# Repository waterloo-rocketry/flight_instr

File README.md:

# flight_instr
This is the flight/engine instrumentation system used in Waterloo Rocketry's 2018 rocket, _Unexploded Ordnance (UXO)_. This repository tracks the hardware and software used in this system. The flight instrumentation PCB is a monolithic board containing an Arduino Nano, an SD card, a digital sensor suite, an analog sensor suite, a radio transceiver, and an H-bridge valve driver. Two copies of this board were used in UXO to successfully launch the rocket to 13000 ft.

This system is no longer in use. It has been replaced by RocketCAN, a collection of boards that implement the functionality of flight instrumentation in a modular manner. The new system is tracked in the `canhw`, `canlib`, and `cansw_*` repositories.

## Injector board assembly

## Vent board assembly

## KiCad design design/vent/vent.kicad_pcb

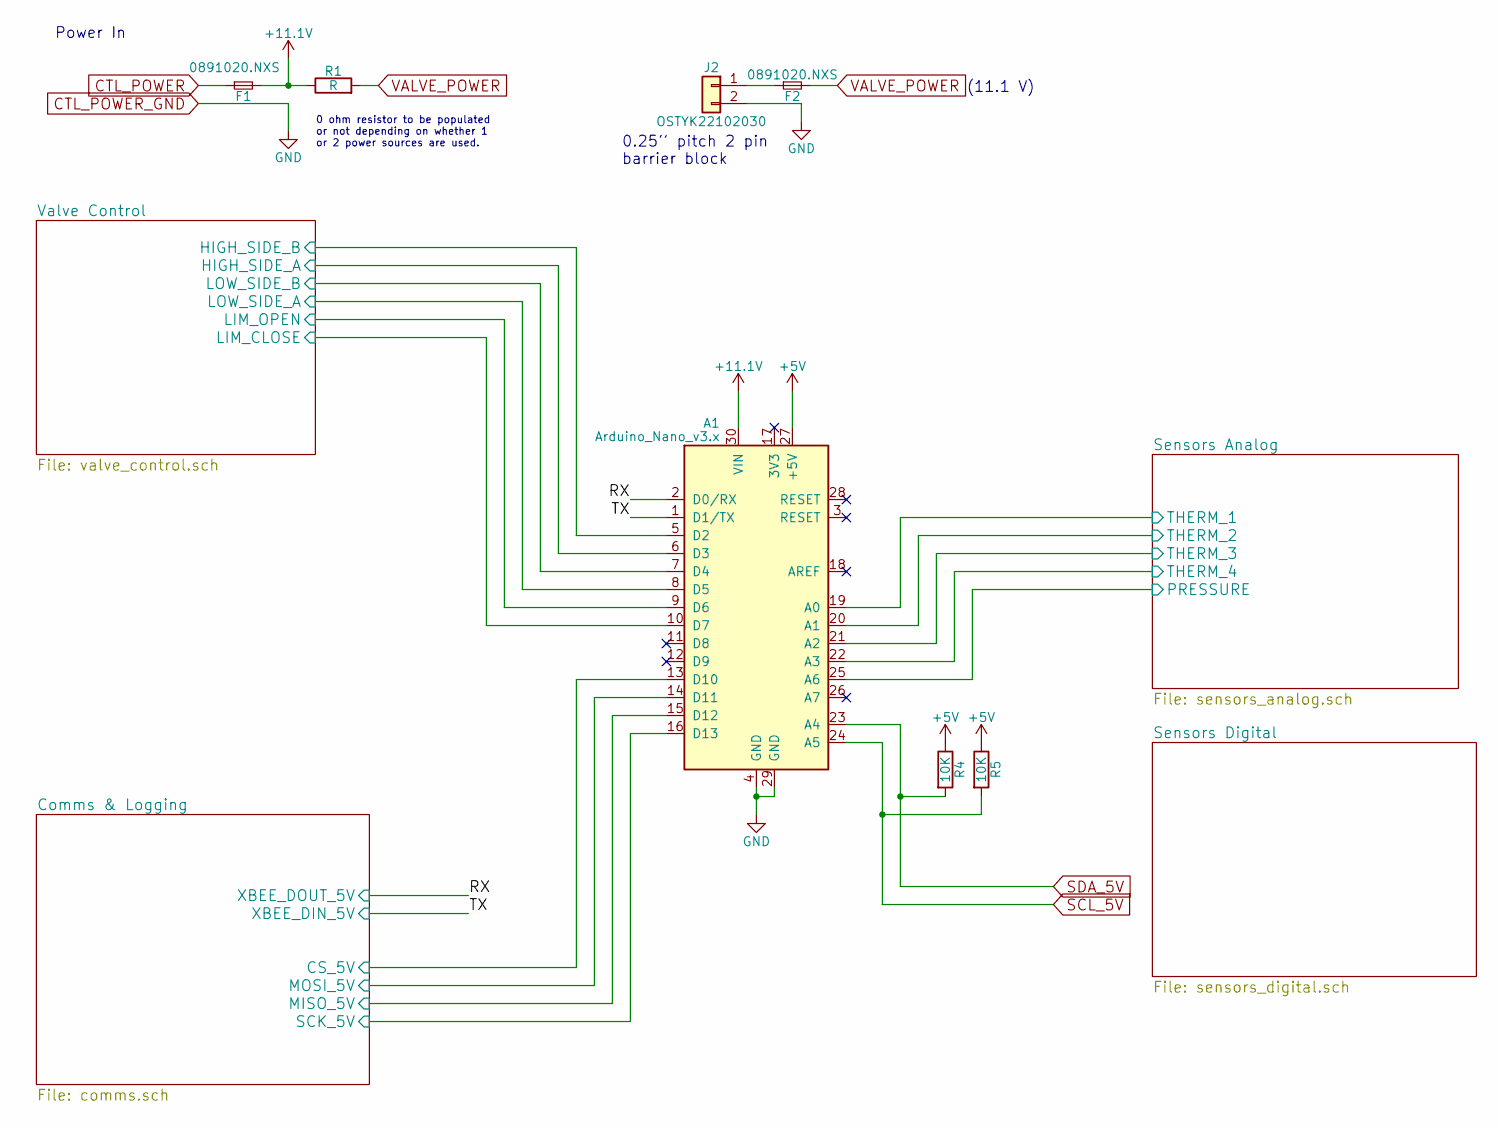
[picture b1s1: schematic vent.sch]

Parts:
A1: Arduino_Nano_v3.x; Arduino_Nano
F1, F2: 0891020.NXS; PC_AutoFuse_Holder
J2: OSTYK22102030; Barrier_Strip_2Circuit
R1: R; R_0805_HandSoldering
R4, R5: 10K; R_0805_HandSoldering

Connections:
+5V: A1.27 (+5V), R4.1, R5.1; also elsewhere on the board
+11.1V: A1.30 (VIN), F1.2, R1.1; also elsewhere on the board
/Comms & Logging/CS_5V: A1.13 (D10); also elsewhere on the board
/Comms & Logging/MISO_5V: A1.15 (D12); also elsewhere on the board
/Comms & Logging/MOSI_5V: A1.14 (D11); also elsewhere on the board
/Comms & Logging/SCK_5V: A1.16 (D13); also elsewhere on the board
/RX: A1.2 (D0/RX); also elsewhere on the board
/Sensors Analog/PRESSURE: A1.25 (A6); also elsewhere on the board
/Sensors Analog/THERM_1: A1.19 (A0); also elsewhere on the board
/Sensors Analog/THERM_2: A1.20 (A1); also elsewhere on the board
/Sensors Analog/THERM_3: A1.21 (A2); also elsewhere on the board
/Sensors Analog/THERM_4: A1.22 (A3); also elsewhere on the board
/TX: A1.1 (D1/TX); also elsewhere on the board
/Valve Control/HIGH_SIDE_A: A1.6 (D3); also elsewhere on the board
/Valve Control/HIGH_SIDE_B: A1.5 (D2); also elsewhere on the board
/Valve Control/LIM_CLOSE: A1.10 (D7); also elsewhere on the board
/Valve Control/LIM_OPEN: A1.9 (D6); also elsewhere on the board
/Valve Control/LOW_SIDE_A: A1.8 (D5); also elsewhere on the board
/Valve Control/LOW_SIDE_B: A1.7 (D4); also elsewhere on the board
CTL_POWER: F1.1; also elsewhere on the board
CTL_POWER_GND: A1.4 (GND), A1.29 (GND), J2.2; also elsewhere on the board
unnamed: F2.1, J2.1
SCL_5V: A1.24 (A5), R5.2; also elsewhere on the board
SDA_5V: A1.23 (A4), R4.2; also elsewhere on the board
VALVE_POWER: F2.2, R1.2; also elsewhere on the board

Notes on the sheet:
Power In
(11.1 V)
0 ohm resistor to be populated or not depending on whether 1 or 2 power sources are used.
0.25'' pitch 2 pin barrier block

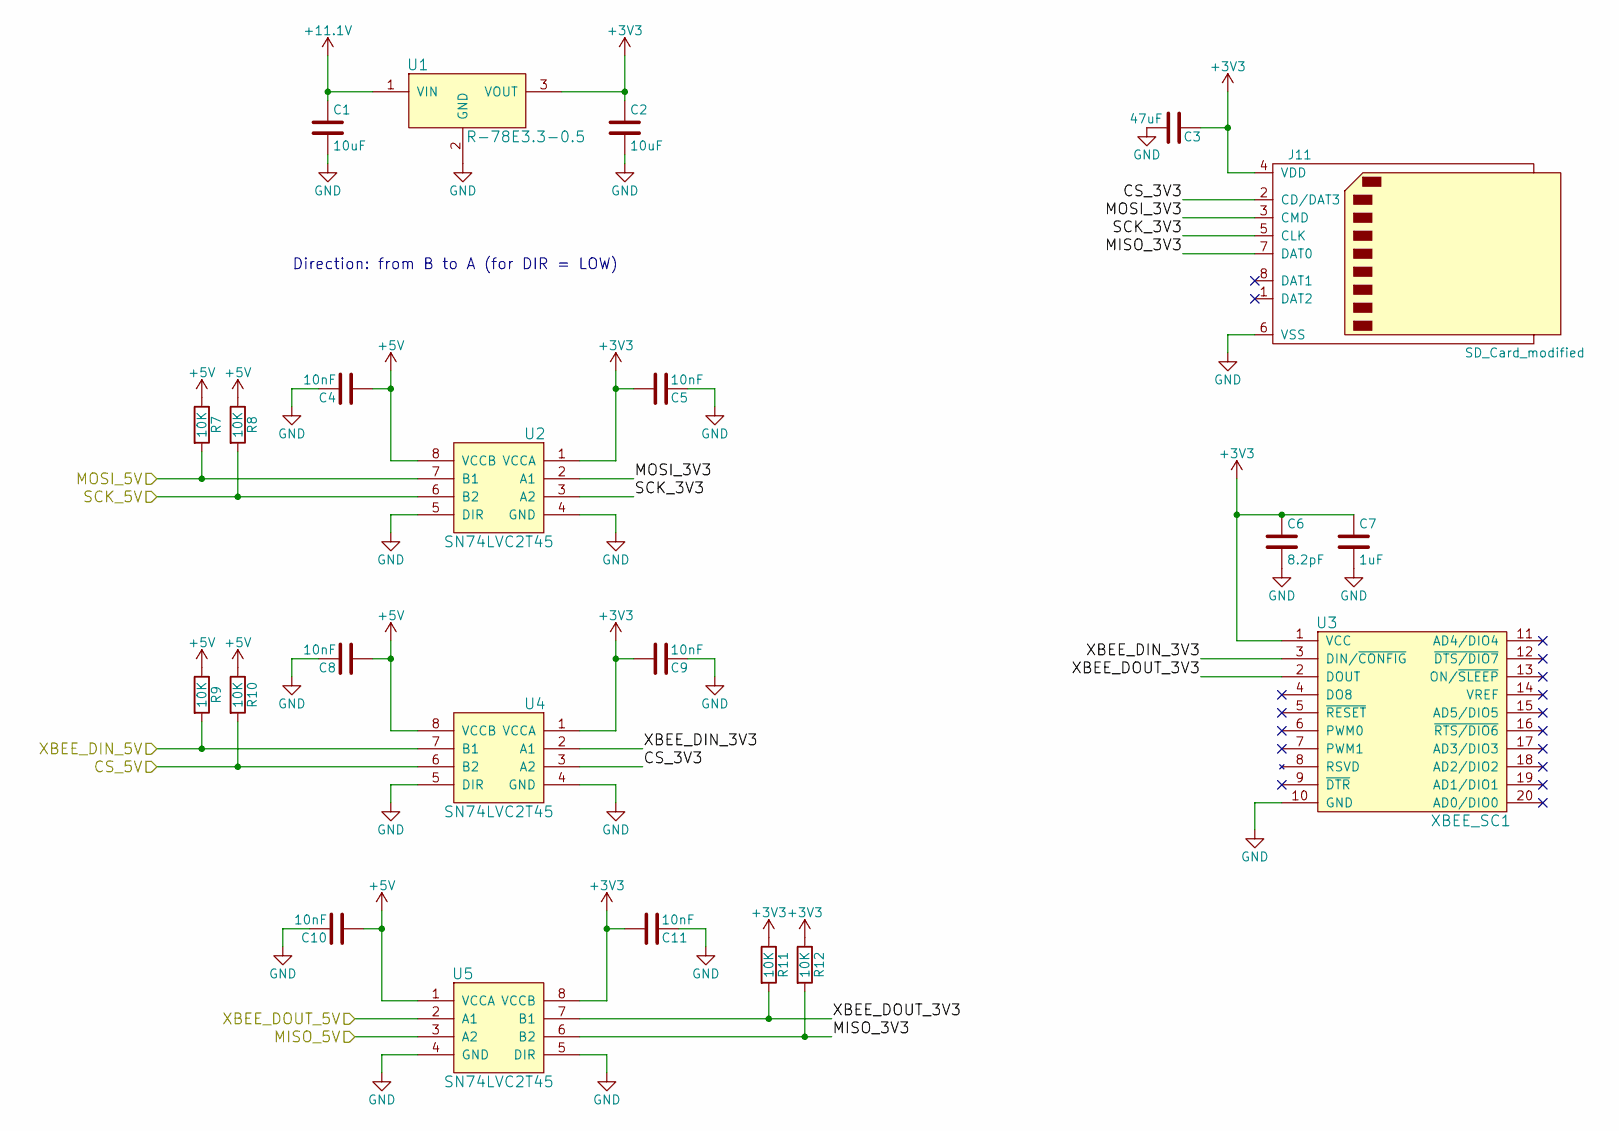
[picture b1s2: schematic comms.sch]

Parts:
C1, C2: 10uF; C_0805_HandSoldering
C3: 47uF; CP_Radial_Tantal_D5.0mm_P2.50mm
C4, C5, C8, C9, C10, C11: 10nF; C_0805_HandSoldering
C6: 8.2pF; C_0805_HandSoldering
C7: 1uF; C_0805_HandSoldering
J11: SD_Card_modified; WM6698CT-ND
R7, R8, R9, R10, R11, R12: 10K; R_0805_HandSoldering
U1: R-78E3.3-0.5; SIP3_11.6x8.5mm
U2, U4, U5: SN74LVC2T45; TSSOP-8_3x3mm_Pitch0.65mm
U3: XBEE_SC1; Xbee_SC1

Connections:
+3V3: C2.1, C3.1, C5.2, C6.1, C7.1, C9.2, C11.2, J11.4 (VDD), R11.1, R12.1, U1.3 (VOUT), U2.1 (VCCA), U3.1 (VCC), U4.1 (VCCA), U5.8 (VCCB)
+5V: C4.2, C8.2, C10.2, R7.1, R8.1, R9.1, R10.1, U2.8 (VCCB), U4.8 (VCCB), U5.1 (VCCA); also elsewhere on the board
+11.1V: C1.1, U1.1 (VIN); also elsewhere on the board
/Comms & Logging/CS_3V3: J11.2 (CD/DAT3), U4.3 (A2)
/Comms & Logging/CS_5V: R10.2, U4.6 (B2); also elsewhere on the board
/Comms & Logging/MISO_3V3: J11.7 (DAT0), R12.2, U5.6 (B2)
/Comms & Logging/MISO_5V: U5.3 (A2); also elsewhere on the board
/Comms & Logging/MOSI_3V3: J11.3 (CMD), U2.2 (A1)
/Comms & Logging/MOSI_5V: R7.2, U2.7 (B1); also elsewhere on the board
/Comms & Logging/SCK_3V3: J11.5 (CLK), U2.3 (A2)
/Comms & Logging/SCK_5V: R8.2, U2.6 (B2); also elsewhere on the board
/Comms & Logging/XBEE_DIN_3V3: U3.3 (DIN/~CONFIG), U4.2 (A1)
/Comms & Logging/XBEE_DOUT_3V3: R11.2, U3.2 (DOUT), U5.7 (B1)
/RX: U5.2 (A1); also elsewhere on the board
/TX: R9.2, U4.7 (B1); also elsewhere on the board
CTL_POWER_GND: C1.2, C2.2, C3.2, C4.1, C5.1, C6.2, C7.2, C8.1, C9.1, C10.1, C11.1, J11.6 (VSS), U1.2 (GND), U2.4 (GND), U2.5 (DIR), U3.10 (GND), U4.4 (GND), U4.5 (DIR), U5.4 (GND), U5.5 (DIR); also elsewhere on the board

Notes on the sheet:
Direction: from B to A (for DIR = LOW)

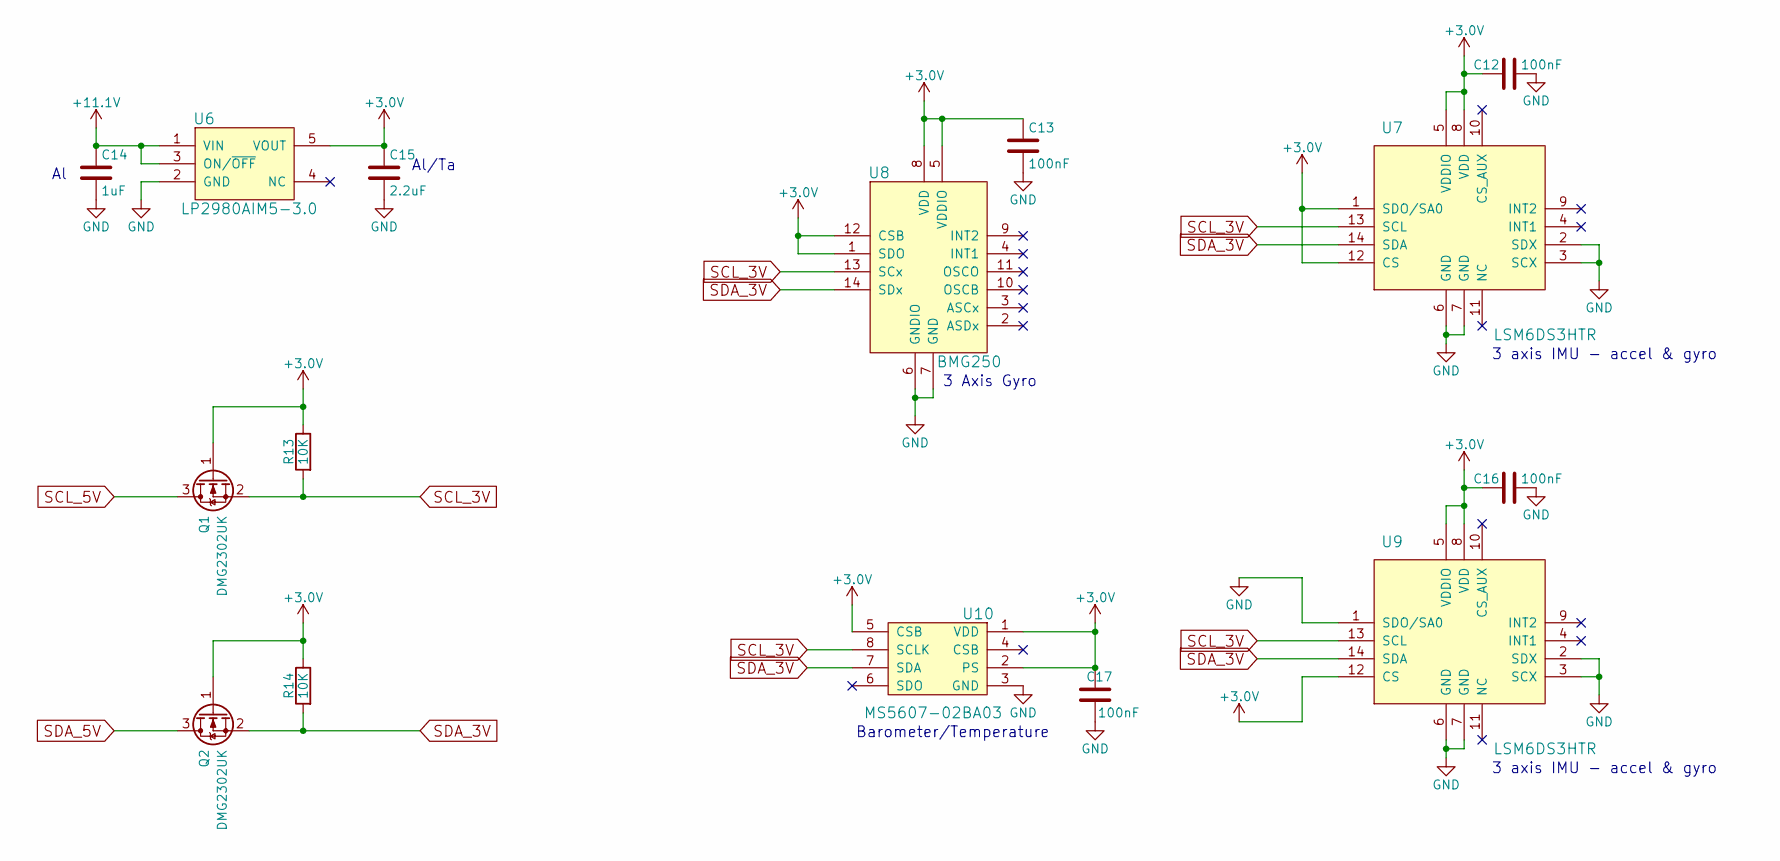
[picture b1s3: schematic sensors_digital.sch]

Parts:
C12, C13, C16, C17: 100nF; C_0805_HandSoldering
C14: 1uF; CP_Radial_Tantal_D5.0mm_P2.50mm
C15: 2.2uF; CP_Radial_Tantal_D5.0mm_P2.50mm
Q1, Q2: DMG2302UK; SOT-23_Handsoldering
R13, R14: 10K; R_0805_HandSoldering
U6: LP2980AIM5-3.0; SOT-23-5_HandSoldering
U7, U9: LSM6DS3HTR
U8: BMG250; Bosch_LGA-14
U10: MS5607-02BA03; MS560702BA03

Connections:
+3.0V: C12.1, C13.1, C15.1, C16.1, C17.1, Q1.1 (G), Q2.1 (G), R13.1, R14.1, U6.5 (VOUT), U7.1 (SDO/SA0), U7.5 (VDDIO), U7.8 (VDD), U7.12 (CS), U8.1 (SDO), U8.5 (VDDIO), U8.8 (VDD), U8.12 (CSB), U9.5 (VDDIO), U9.8 (VDD), U9.12 (CS), U10.1 (VDD), U10.2 (PS), U10.5 (CSB)
+11.1V: C14.1, U6.1 (VIN), U6.3 (ON/~OFF); also elsewhere on the board
CTL_POWER_GND: C12.2, C13.2, C14.2, C15.2, C16.2, C17.2, U6.2 (GND), U7.2 (SDX), U7.3 (SCX), U7.6 (GND), U7.7 (GND), U8.6 (GNDIO), U8.7 (GND), U9.1 (SDO/SA0), U9.2 (SDX), U9.3 (SCX), U9.6 (GND), U9.7 (GND), U10.3 (GND); also elsewhere on the board
SCL_3V: Q1.2 (S), R13.2, U7.13 (SCL), U8.13 (SCx), U9.13 (SCL), U10.8 (SCLK)
SCL_5V: Q1.3 (D); also elsewhere on the board
SDA_3V: Q2.2 (S), R14.2, U7.14 (SDA), U8.14 (SDx), U9.14 (SDA), U10.7 (SDA)
SDA_5V: Q2.3 (D); also elsewhere on the board

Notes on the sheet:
3 axis IMU - accel & gyro
Barometer/Temperature
3 Axis Gyro
Al/Ta

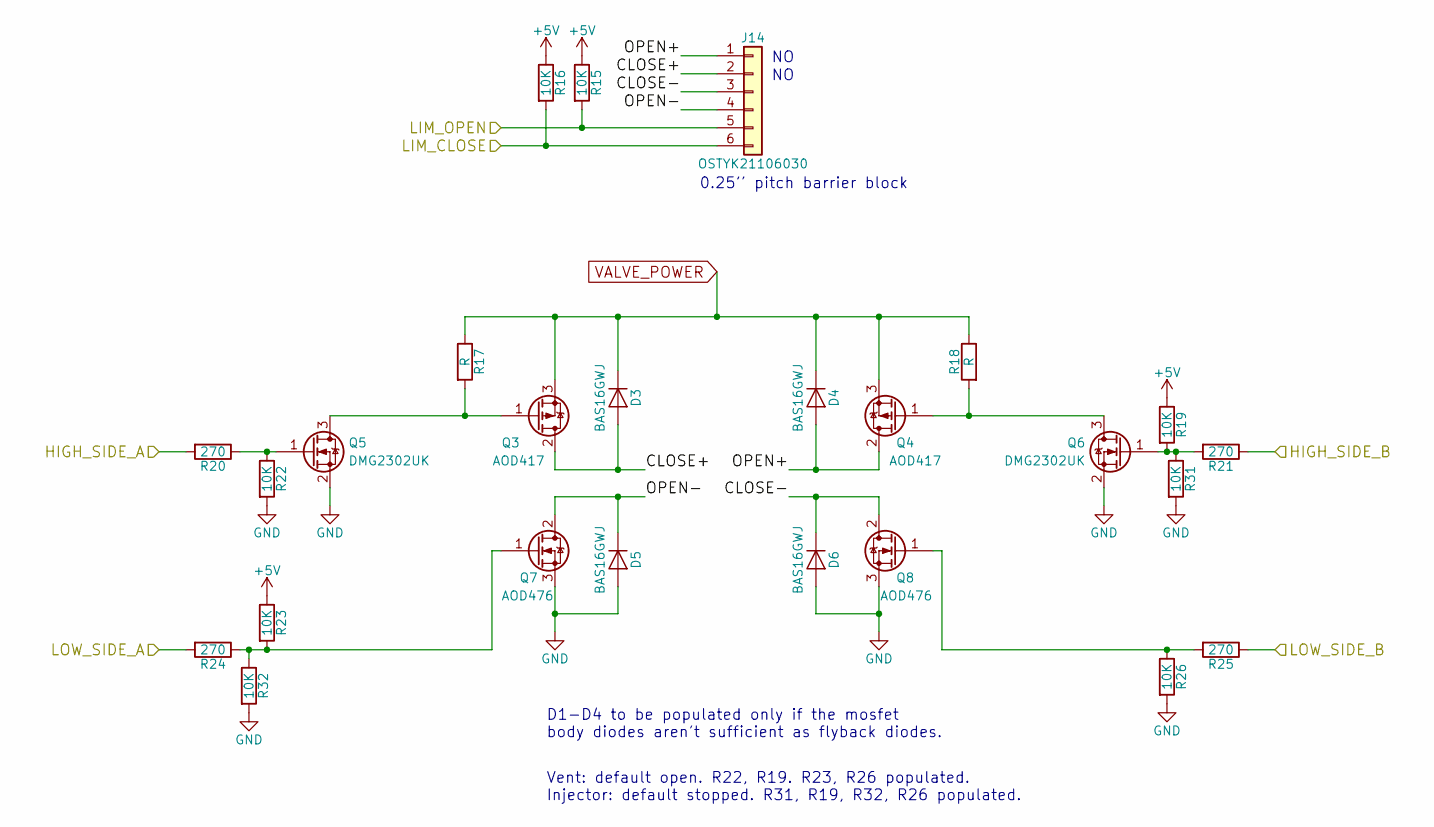
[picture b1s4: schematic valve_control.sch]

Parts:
D3, D4, D5, D6: BAS16GWJ; D_SOD-123_HandSoldering
J14: OSTYK21106030; Barrier_Strip_6Circuit
Q3, Q4: AOD417; TO-252-2
Q5, Q6: DMG2302UK; SOT-23_Handsoldering
Q7, Q8: AOD476; TO-252-2
R15, R16, R19, R22, R23, R26, R31, R32: 10K; R_0805_HandSoldering
R17, R18: R; R_0805_HandSoldering
R20, R21, R24, R25: 270; R_0805_HandSoldering

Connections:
+5V: R15.1, R16.1, R19.1, R23.1; also elsewhere on the board
/Valve Control/CLOSE+: D3.2 (A), J14.2, Q3.2 (D)
/Valve Control/CLOSE-: D6.1 (K), J14.3, Q8.2 (D)
/Valve Control/HIGH_SIDE_A: R20.2; also elsewhere on the board
/Valve Control/HIGH_SIDE_B: R21.1; also elsewhere on the board
/Valve Control/LIM_CLOSE: J14.6, R16.2; also elsewhere on the board
/Valve Control/LIM_OPEN: J14.5, R15.2; also elsewhere on the board
/Valve Control/LOW_SIDE_A: R24.2; also elsewhere on the board
/Valve Control/LOW_SIDE_B: R25.1; also elsewhere on the board
/Valve Control/OPEN+: D4.2 (A), J14.1, Q4.2 (D)
/Valve Control/OPEN-: D5.1 (K), J14.4, Q7.2 (D)
CTL_POWER_GND: D5.2 (A), D6.2 (A), Q5.2 (S), Q6.2 (S), Q7.3 (S), Q8.3 (S), R22.2, R26.2, R31.2, R32.2; also elsewhere on the board
unnamed: Q3.1 (G), Q5.3 (D), R17.2
unnamed: Q4.1 (G), Q6.3 (D), R18.2
unnamed: Q5.1 (G), R20.1, R22.1
unnamed: Q6.1 (G), R19.2, R21.2, R31.1
unnamed: Q7.1 (G), R23.2, R24.1, R32.1
unnamed: Q8.1 (G), R25.2, R26.1
VALVE_POWER: D3.1 (K), D4.1 (K), Q3.3 (S), Q4.3 (S), R17.1, R18.1; also elsewhere on the board

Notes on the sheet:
D1-D4 to be populated only if the mosfet body diodes aren't sufficient as flyback diodes.
Vent: default open. R22, R19. R23, R26 populated. Injector: default stopped. R31, R19, R32, R26 populated.
0.25'' pitch barrier block

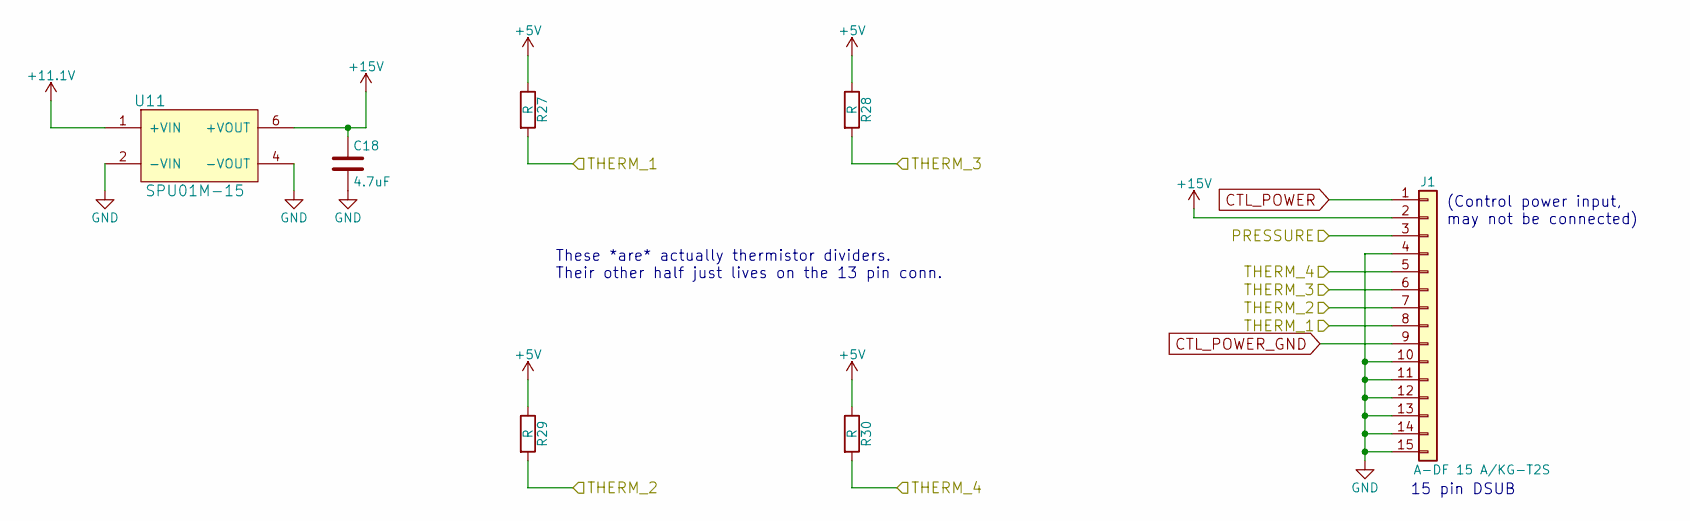
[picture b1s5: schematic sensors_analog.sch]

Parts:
C18: 4.7uF; C_0805_HandSoldering
J1: A-DF 15 A/KG-T2S; DSUB-15_Male_Horizontal_P2.77x2.84mm_EdgePinOffset7.70mm_Ho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
R27, R28, R29, R30: R; R_0805_HandSoldering
U11: SPU01M-15; SIP6_Housing

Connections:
+5V: R27.1, R28.1, R29.1, R30.1; also elsewhere on the board
+11.1V: U11.1 (+VIN); also elsewhere on the board
+15V: C18.1, J1.2, U11.6 (+VOUT)
/Sensors Analog/PRESSURE: J1.3; also elsewhere on the board
/Sensors Analog/THERM_1: J1.8, R27.2; also elsewhere on the board
/Sensors Analog/THERM_2: J1.7, R29.2; also elsewhere on the board
/Sensors Analog/THERM_3: J1.6, R28.2; also elsewhere on the board
/Sensors Analog/THERM_4: J1.5, R30.2; also elsewhere on the board
CTL_POWER: J1.1; also elsewhere on the board
CTL_POWER_GND: C18.2, J1.4, J1.9, J1.10, J1.11, J1.12, J1.13, J1.14, J1.15, U11.2 (-VIN), U11.4 (-VOUT); also elsewhere on the board

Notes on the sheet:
(Control power input, may not be connected)
These *are* actually thermistor dividers. Their other half just lives on the 13 pin conn.
15 pin DSUB

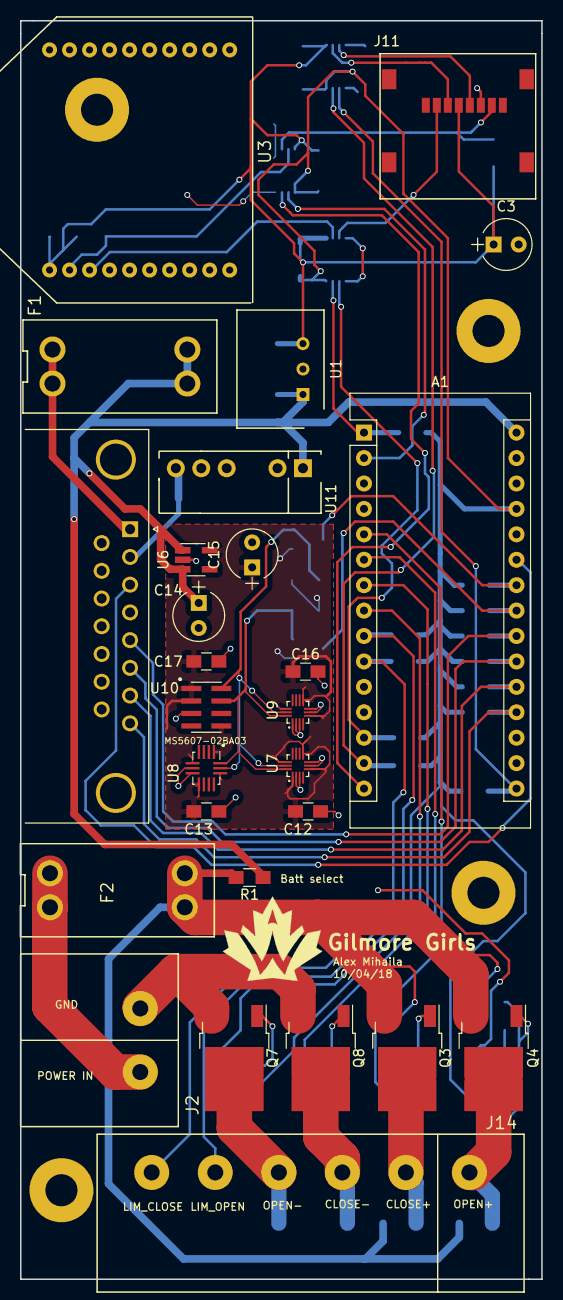
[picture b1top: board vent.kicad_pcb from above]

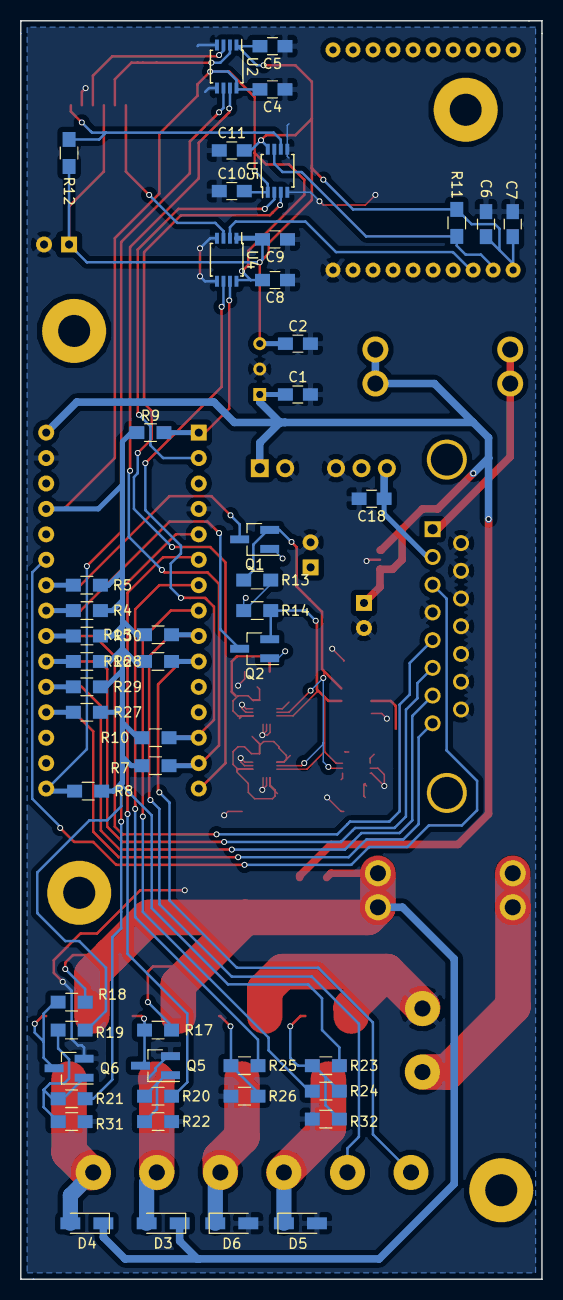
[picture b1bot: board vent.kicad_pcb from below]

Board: 2 copper layers, 52.1 x 125.7 mm, 77 parts (50 on the bottom side), 46 nets.

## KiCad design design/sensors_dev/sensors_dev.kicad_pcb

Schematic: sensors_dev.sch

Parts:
A1: Arduino_Nano_v3.x; Arduino_Nano
C1: 1uF; CP_Radial_Tantal_D5.0mm_P2.50mm
C2: 2.2uF; CP_Radial_Tantal_D5.0mm_P2.50mm
J1: Conn_01x02; Pin_Header_Straight_1x02_Pitch2.54mm
J2, J3: Conn_01x15; Pin_Header_Straight_1x15_Pitch2.54mm
Q1, Q2: RE1C002UN; SOT-23_Handsoldering
R1, R2, R3, R4: 10K; R_0805_HandSoldering
U1: LP2980AIM5-3.0; SOT-23-5_HandSoldering

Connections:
+3.0V: C2.1, Q1.1 (G), Q2.1 (G), R2.1, R4.1, U1.5 (VOUT); also elsewhere on the board
+5V: J2.1, R1.1, R3.1
+7.5V: C1.1, J1.1, J2.2, U1.1 (VIN), U1.3 (ON/~OFF)
/SCL_5V: J2.3, Q1.3 (D), R1.2
/SDA_5V: J2.4, Q2.3 (D), R3.2
GND: C1.2, C2.2, J1.2, J2.5, U1.2 (GND); also elsewhere on the board
SCL_3V: Q1.2 (S), R2.2; also elsewhere on the board
SDA_3V: Q2.2 (S), R4.2; also elsewhere on the board

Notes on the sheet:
Al/Ta
(12V also good)

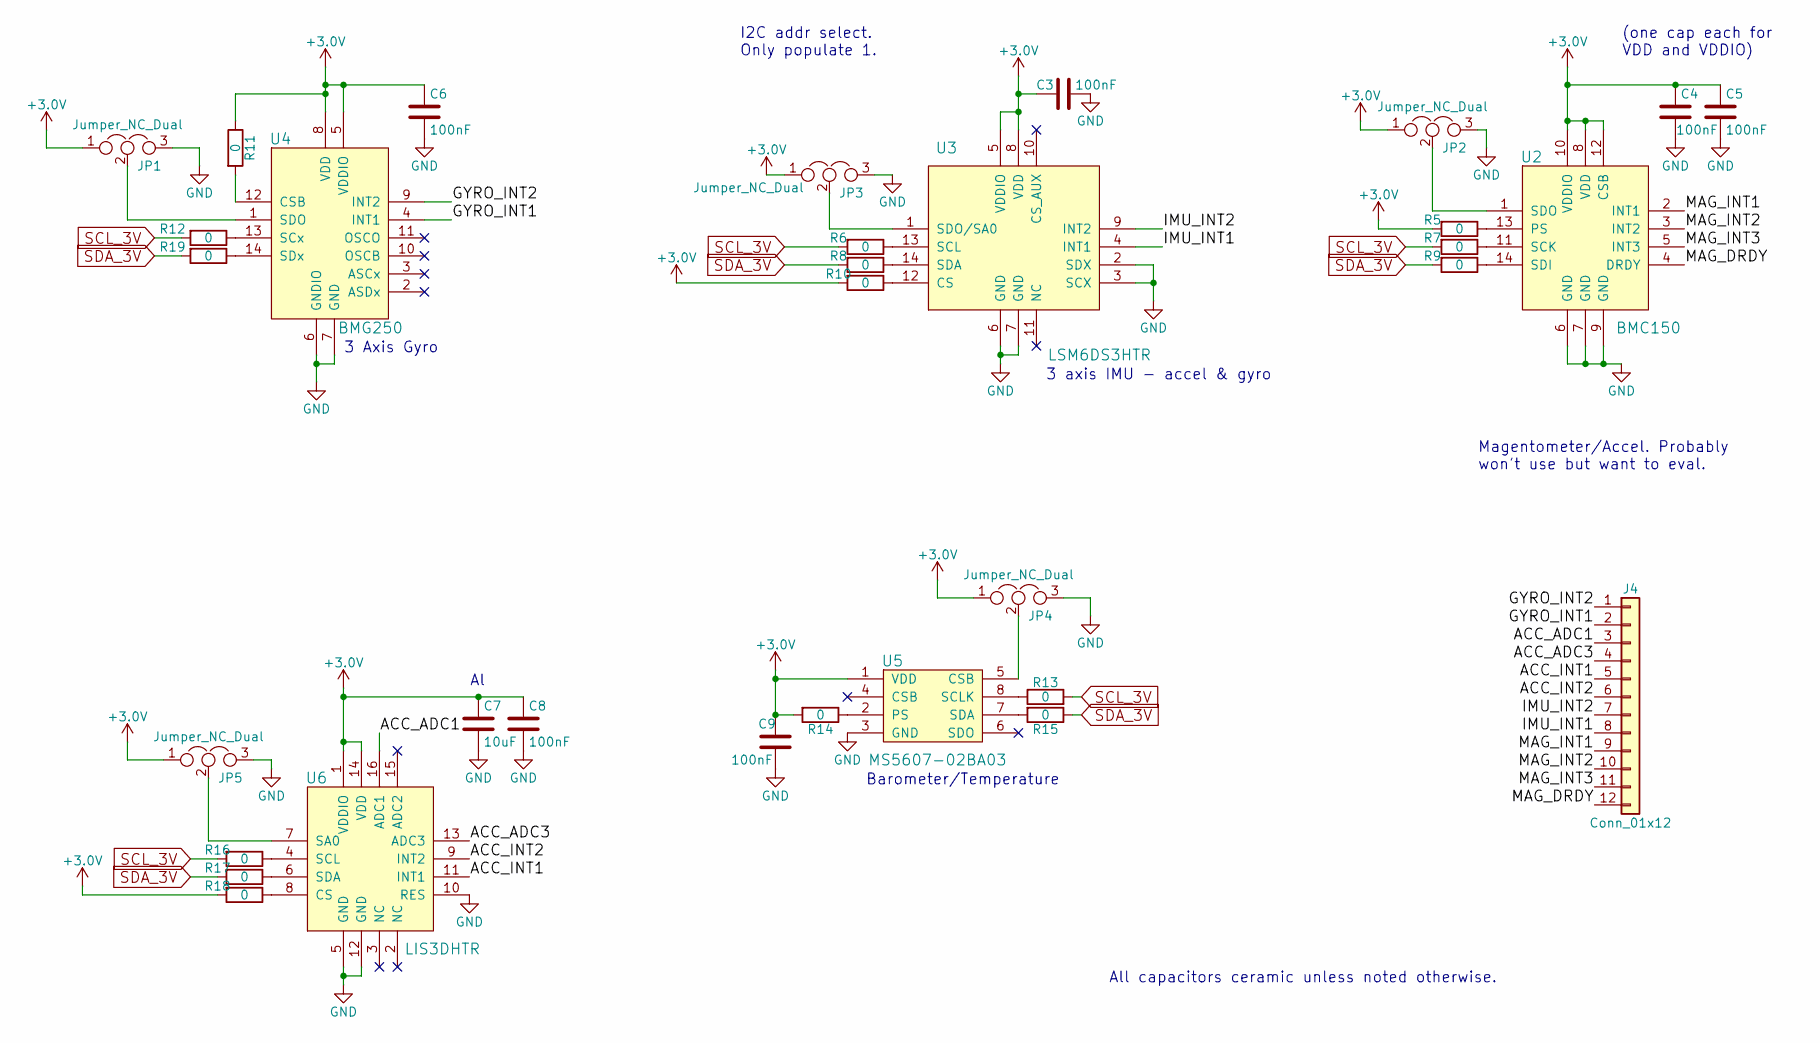
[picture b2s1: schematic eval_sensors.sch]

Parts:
C3, C4, C5, C6, C8, C9: 100nF; C_0603_HandSoldering
C7: 10uF; CP_Radial_Tantal_D5.0mm_P2.50mm
J4: Conn_01x12; Pin_Header_Straight_1x12_Pitch2.54mm
JP1, JP2, JP3, JP4, JP5: Jumper_NC_Dual; Pin_Header_Straight_1x03_Pitch2.54mm
R5, R6, R7, R8, R9, R10, R13, R14, R15, R16, R17, R18: 0; R_0603_HandSoldering
R11, R12, R19: 0; C_0603_HandSoldering
U2: BMC150; Bosch_LGA-14
U3: LSM6DS3HTR; PQFN50P300X250X86-14N
U4: BMG250; Bosch_LGA-14
U5: MS5607-02BA03; MS560702BA03
U6: LIS3DHTR; LGA16_LIS3DHTR

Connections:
+3.0V: C3.1, C4.1, C5.1, C6.1, C7.1, C8.1, C9.1, JP1.1, JP2.1, JP3.1, JP4.1, JP5.1, R5.2, R10.2, R11.1, R14.2, R18.2, U2.8 (VDD), U2.10 (VDDIO), U2.12 (CSB), U3.5 (VDDIO), U3.8 (VDD), U4.5 (VDDIO), U4.8 (VDD), U5.1 (VDD), U6.1 (VDDIO), U6.14 (VDD); also elsewhere on the board
/Eval Sensors/ACC_ADC1: J4.3, U6.16 (ADC1)
/Eval Sensors/ACC_ADC3: J4.4, U6.13 (ADC3)
/Eval Sensors/ACC_INT1: J4.5, U6.11 (INT1)
/Eval Sensors/ACC_INT2: J4.6, U6.9 (INT2)
/Eval Sensors/GYRO_INT1: J4.2, U4.4 (INT1)
/Eval Sensors/GYRO_INT2: J4.1, U4.9 (INT2)
/Eval Sensors/IMU_INT1: J4.8, U3.4 (INT1)
/Eval Sensors/IMU_INT2: J4.7, U3.9 (INT2)
/Eval Sensors/MAG_DRDY: J4.12, U2.4 (DRDY)
/Eval Sensors/MAG_INT1: J4.9, U2.2 (INT1)
/Eval Sensors/MAG_INT2: J4.10, U2.3 (INT2)
/Eval Sensors/MAG_INT3: J4.11, U2.5 (INT3)
GND: C3.2, C4.2, C5.2, C6.2, C7.2, C8.2, C9.2, JP1.3, JP2.3, JP3.3, JP4.3, JP5.3, U2.6 (GND), U2.7 (GND), U2.9 (GND), U3.2 (SDX), U3.3 (SCX), U3.6 (GND), U3.7 (GND), U4.6 (GNDIO), U4.7 (GND), U5.3 (GND), U6.5 (GND), U6.10 (RES), U6.12 (GND); also elsewhere on the board
unnamed: JP1.2, U4.1 (SDO)
unnamed: JP2.2, U2.1 (SDO)
unnamed: JP3.2, U3.1 (SDO/SA0)
unnamed: JP4.2, U5.5 (CSB)
unnamed: JP5.2, U6.7 (SA0)
unnamed: R5.1, U2.13 (PS)
unnamed: R6.1, U3.13 (SCL)
unnamed: R7.1, U2.11 (SCK)
unnamed: R8.1, U3.14 (SDA)
unnamed: R9.1, U2.14 (SDI)
unnamed: R10.1, U3.12 (CS)
unnamed: R11.2, U4.12 (CSB)
unnamed: R12.1, U4.13 (SCx)
unnamed: R13.1, U5.8 (SCLK)
unnamed: R14.1, U5.2 (PS)
unnamed: R15.2, U5.7 (SDA)
unnamed: R16.1, U6.4 (SCL)
unnamed: R17.1, U6.6 (SDA)
unnamed: R18.1, U6.8 (CS)
unnamed: R19.1, U4.14 (SDx)
SCL_3V: R6.2, R7.2, R12.2, R13.2, R16.2; also elsewhere on the board
SDA_3V: R8.2, R9.2, R15.1, R17.2, R19.2; also elsewhere on the board

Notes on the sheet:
I2C addr select. Only populate 1.
3 axis IMU - accel & gyro
Barometer/Temperature
Magentometer/Accel. Probably won't use but want to eval.
All capacitors ceramic unless noted otherwise.
(one cap each for VDD and VDDIO)
3 Axis Gyro

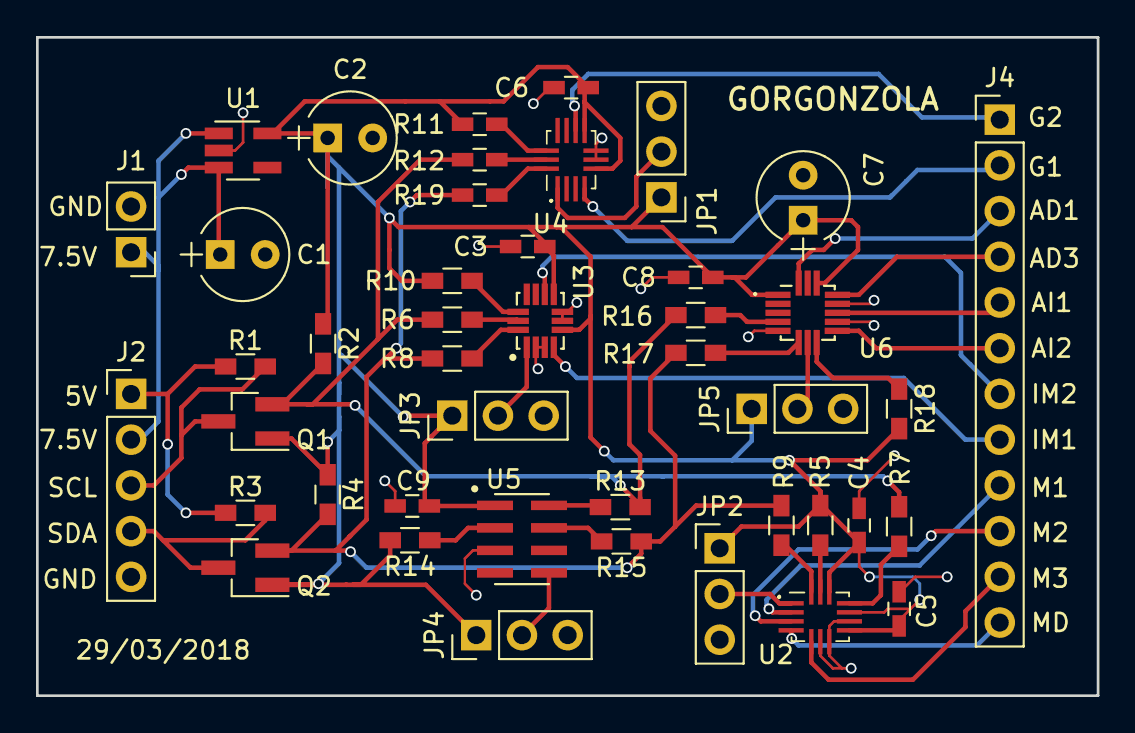
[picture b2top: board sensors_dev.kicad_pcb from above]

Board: 2 copper layers, 58.9 x 36.6 mm, 44 parts (0 on the bottom side), 40 nets.

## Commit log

2018-03-03 Initial commit
    Linear actuator board schematic, sanity check software, and datasheets.
2018-03-09 Specify part numbers for the H bridge MOSFETS
2018-03-17 First draft of sensor development board
2018-03-17 fix FXAS21002 protocol and bidir mosfets
    - Per review, tie pin 17 of FXAS21002 to HIGH the way it should be for
    I2C mode.
    - switch out bidirectional mosfets for some that would actually work.
    (VGS_th too hih relative to VDS for the old ones)
2018-03-17 Add footprints and decoupling caps to some ICs
2018-03-20 Start PCB and swap out gyro
    Old gyro (fxas) was 24 LGA and required a clearance between 3 and 4 mil,
    which increases costs and cuts down fab house options. Swapped out the
    gyro for another one with slightly higher drift but in a more convenient
    package (LGA14).
2018-03-20 First draft PCB layout
    Todo: move arduino off board (use a breadboard instead). Will save a lot
    of space on the PCB and make the prototype cheaper.
2018-03-27 First pass board routing.
    Also, remove arduino from PCB since this is a dev board and there's no
    point paying for extra unused board space.
2018-03-29 Redo board placement and routing
    Will send to fab after final review.
2018-03-29 Minor review changes
    Move C9 and R14 further away from U5.
2018-05-01 Add dev board gerbers
    Requirements:
    5/5 mil trace/clearance
2018-05-01 Flight instr Injector/Vent schematic (1st Draft)
    Includes:
    - Arduino nano (rev3)
    - Xbee SC1
    - MicroSD card
    - Valve control
    - Analog sensors (thermistors & pressure)
2018-05-04 Refine schematic
    - Add part numbers and correct pinout for mosfets
    - Add fuses to battery inputs
    - Add decoupling caps to logic translators
    - Add flyback diodes to H Bridge, to be populated if the body diodes of
    the mosfets are not sufficient.
    - Change H Bridge to operate with 4 inputs instead of 2.
2018-05-06 Review changes
    - Add debug LEDs
    - Add pullup resistors on logic shifters for xbee and sd card.
    - Add 0 ohm resistor between valve and control power sources (to allow
    for either one of both sources to be used).
    - Add another IMU
    - Add gate resistors to valve control mosfets
2018-05-06 Fix MOSFET gate resistors
2018-05-07 Break out I2C lines on dsub connector
2018-05-07 Add support for injector valve default state
2018-05-08 Add connector part numbers to schematic
2018-05-08 Add barrier block footprints
2018-05-08 Add MicroSD card socket PCB footprint
    Based on the datasheet drawing found at https://www.molex.com/pdm_docs/sd/472192001_sd.pdf
2018-05-08 Add more part numbers and footprints
    - Flyback diodes
    - Fuses
    - Xbee
2018-05-08 Add LED part numbers
2018-05-09 Fix pullups/pulldowns for injector default
2018-05-09 Create BOM
2018-05-09 Whitespace fixes
2018-05-09 Vent & Injector Board Layout
2018-05-10 Final vent/injector layout + routing
2018-05-10 Add vent/injector gerbers
2018-05-10 Tweak 3V pour, regenerate gerbers
2018-05-10 Update silkscreen, regen gerbers
2018-05-12 Add solderpaste layer to Gerbers
2018-05-12 Add dimensions for Gilmore Girls
2018-05-19 Add valve wiring docs and BOM
2018-05-20 Add rlcs dependency as submodule
    Also, Makefile improvements (put object files in their own directory).
2018-05-20 Kicad project cleanup
    - Remove backup files
    - Fix rescued components
2018-05-23 Add debug version of IMU driver
    Currently includes support for configuring and reading from the
    accelerometer and gyroscope. Debug version only: results are printed
    directly over serial.
    Cleanup to be done:
    - better handling of ord, fs, and other datasheet parameters
    - better organization of output data and whatnot
2018-05-26 Test nodeio.ioio integration
2018-06-02 RLCS upstream changes lol
2018-06-02 Correct pressure sensor calibration factors
2018-06-05 Minor makefile fixes
    Change makefile to allow for macro definition at the command line (for
    NODE_VENT and NODE_INJ). Also, add README explaining this.
2018-06-05 WIP IREC packing list
    TODO: add quanitites, double check items
2018-06-09 Add 3rd party barometer library
    Tested, it works. It might get swapped out for my own driver if I have
    time and feel like it. For now this is fine.
2018-06-10 Debug version of BMG250 driver
    Implement proper configuration and readout. Still need to apply
    calibration offsets, choose proper ranges, and refactor into a better
    form.
2018-06-10 Update IREC packing list
    - add radios, nylon screws, spare arduinos
    - remove dupont crimpers
2018-06-11 Add SD prelim SD support
2018-06-11 wip refactor do not commit
2018-06-11 Clean up gyro code
2018-06-12 Add main loop and do some cleanup
2018-06-12 Add sd init
    TODO: actually write data to the damn thing
2018-06-15 Make SD logging work
    Still full of debug printfs -> will need to remove these.
2018-06-16 Code cleanup
    - Clean up gyro and imu drivers.
    - Correct IMU address in main
    - Remove all the debug serial prints
2018-06-20 Fix accel scaling and thermistor pin numbers
2018-06-27 Create LICENSE for code portion
2018-06-27 Move GPL file to software dir
2018-06-27 Release hardware designs under MIT license
2019-06-21 Add photos of PCBs
2019-06-21 Add readme
2019-06-21 rename photos
2019-06-21 Add photos to readme
